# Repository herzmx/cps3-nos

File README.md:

# CPS3 NOS (NOR Open SIMM)

CPS3 NOS is an alternative to the original SIMMs for CPS3; currently, the available options include clone SIMMs with old-stock FLASH memory and Ultra SIMMs by DS. 

The project shares similarities with UltraSIMM but is not based on it. Instead, it is a new implementation built using publicly available pinouts and CPS3 schematics from FPGA projects.

The initial design aimed to use SPANSION NOR FLASH as the main memory, but this proved unfeasible due to speed limitations causing significant instability. As a result, MICRON NOR FLASH was used instead. While this is the same type of memory used in UltraSIMM and shares its pinout, but it's not directly compatible with UltraSIMM/UltraBIOS setup, because it is an entirely separate implementation.

The primary purpose of this project is to provide an alternative to SIMMs for catridges with original keys and battery, addressing the risks involved when updating the BIOS using the [CPS3 SIMM/CARTRIDGE PORT ADAPTER for OSCR](https://github.com/herzmx/CPS3-OSCR-Adapter). This project is not intended to create a new multi-SIMM solution. Given this primary purpose, it is very likely that UltraSIMM would also works on catridges with original keys and battery, though I do not have access to one to confirm.

## Issue Detected on 128MB NOS Module (Resolved)

An issue was previously identified with the 128MB NOS module, causing intermittent problems after extended use and potentially impacting game performance.

This has been fixed by replacing the LS148 logic with LVC00 and LVC08 gates to handle bank switching on the 128MB memory. This change improved response speed, resulting in consistent and stable reads.

If you built a module before this fix, we recommend updating to the latest source files.

## Assembly/Production  

Gerber, BOM, and POS files are provided in the `hw` directory. You can send them directly to a PCB fabrication company or assemble the boards yourself.  

When assembling, consider that the minimum pitch is **0.5mm**, and the footprint for capacitors and resistors is **0603**.

**Important!!!**, PCB tickness it's **1.2mm**

### 64MB SIMM  

For 64MB SIMMs, you can use the following parallel NOR FLASH memory chips:  

- **Micron MT28EW256/512/01G**  
- **Spansion S29256/512/GL01G** (use the 100ns speed version)  

### 128MB SIMM  

For 128MB SIMMs, only **Micron MT28EW01G** parallel NOR FLASH is supported. During development and testing, **Spansion** memory did not work as expected with bank switching on the 128MB SIMM.  

### Notes  

- Use only one type of SIMM when assembling a single **64MB SIMM**.  
- You can mix **Micron** and **Spansion** SIMMs if needed.  

## How to use

CPS3 can only handle four types of FLASH memory due to the instructions used for flashing new games through the system, these instructions are supported and coded in the BIOS.  

To make a new NOR FLASH memory compatible with CPS3, a BIOS patch is required.

### BIOS Patch

The **bios_patch.py** script allows you to apply patches to your current BIOS, adding compatibility for **SPANSION** and **MICRON** NOR FLASH.

For example, if you have a dump of *Street Fighter III 3rd Strike*, you can execute the following command to patch BIOS:

```bash
python bios_patch.py sfiii3_usa.29f400.u2 sfiii3
```

#### Compatibility Table

| Before patch | After patch          |
|--------------|----------------------|
| MXCI         | MXCI                 |
| SHARP/INTEL  | SHARP/INTEL          |
| HITACHI      | SPANSION             |
| MXIC         | MICRON NOS/UltraSIMM |

### Flashing Your New BIOS

Once the patch is applied, it's time to flash your updated BIOS onto the cartridge. There are two main methods you can use:

1. **Using the [CPS3 SIMM/CARTRIDGE PORT ADAPTER for OSCR](https://github.com/herzmx/CPS3-OSCR-Adapter)**  
   - This method works for both alive and death cartridges.
   - **NOTE**: Use it at your own risk on alive cartridges!

2. **Traditional Method**  
   - Remove the 29F400 chip from the cartridge and flash it using a programmer.  
   - This method is only recommended for death cartridges.

Now your cartdrige it's compatible with NOS!

### R/W CPS3 NOS 

Currently, CPS3 NOS can only be programmed using the [CPS3 SIMM/CARTRIDGE PORT ADAPTER for OSCR](https://github.com/herzmx/CPS3-OSCR-Adapter).

#### Prepare your files 

- **Dump or copy**  your CD-ROM files and organize them into a directory. For example, for *Street Fighter III: 2nd Impact*, the directory structure should look like this:

	```
    CDROM
    └── SFIII2
        ├── 10
        ├── 20
        ├── 30
        ├── 31
        ├── 40
        ├── 41
        ├── 50
        ├── 51
        ├── 90
        ├── 91
        ├── 92
        └── 93
	```

- Concatenate files for each SIMM
	- For **128M SIMMs**, use files 3# to 6#. 
	- For **64M SIMMs**, use files 10 and 20.
	
	 Example (using a Unix terminal):
	 
	 ```bash
	 	cat WAZARD/10WZ SFIII/10NG SFIII2/10 JOJO/10JO SFIII3B/103S2 JOJOBA/10JB > NOS10

		cat WAZARD/10WZFix SFIII/10NG SFIII2/10 JOJO/10JO SFIII3B/103S2 JOJOBA/10JB > NOS10
		
		cat WAZARD/20WZ SFIII/20NG SFIII2/20 JOJO/20JO SFIII3B/203S2 JOJOBA/20JB > NOS20
		
		cat WAZARD/30WZ WAZARD/31WZ SFIII/30NG SFIII/31NG SFIII2/30 SFIII2/31 JOJO/30JO JOJO/31JO SFIII3B/303S2 SFIII3B/313S2 JOJOBA/30JB JOJOBA/31JB > NOS30
		
		cat WAZARD/40WZ WAZARD/41WZ SFIII/40NG SFIII/41NG SFIII2/40 SFIII2/41 JOJO/40JO JOJO/41JO SFIII3B/403S2 SFIII3B/413S2 JOJOBA/40JB JOJOBA/41JB > NOS40
		
		cat WAZARD/50WZ WAZARD/51WZ SFIII/50NG SFIII/51NG SFIII2/50 SFIII2/51 JOJO/50JO JOJO/51JO SFIII3B/503S2 SFIII3B/513S2 JOJOBA/50JB JOJOBA/51JB > NOS50
		
		cat WAZARD/60WZ WAZARD/61WZ SFIII/60NG SFIII/61NG SFIII2/60 SFIII2/61 JOJO/60JO JOJO/61JO SFIII3B/603S2 SFIII3B/613S2 JOJOBA/60JB JOJOBA/61JB > NOS60
	 ```
	 
**Important Notes**
 
- NOS supports up to 8 titles. When using this feature, you must fill all SIMM slots and space.
- For example, when working with *Street Fighter III: New Generation*, you can duplicate certain files to fill all space:
- Use `10` as `20` for SIMM 2.
- Use `50` four times for SIMM 5.
- Use `40` as `60 `for SIMM 6.
 	
|                                             | 1      | 2      | 3       | 4       | 5       | 6       |
|---------------------------------------------|--------|--------|---------|---------|---------|---------|
| Street Fighter III: New Generation          | 64MBit | -      | 128MBit | 128MBit | 32MBit  | -       |
| Street Fighter III: New Generation (filled) | 64MBit | 64MBit | 128MBit | 128MBit | 128MBit | 128MBit |

Alternatively, you can use the **ds2nos.py** script to convert UltraSIMM files to NOS format.

#### Write NOS

The [CPS3 SIMM/CARTRIDGE PORT ADAPTER for OSCR](https://github.com/herzmx/CPS3-OSCR-Adapter) has designated slots for 64M and 128M SIMMs. Insert your NOS into the corresponding slot and connect the headers for additional addressing.

- Prepare your SD, copy NOS10* to NOS60* in root
- Use *Capcom System III* menu options to write files
- 128 MB

- 64 MB

### Install NOS on CPS3

- After writing all the NOS, install the SIMMs into the CPS3. It is recommended to label each SIMM to prevent any mix-ups in the future.

- Install the SW header to link all NOS if you plan to use more than one title.

### NOS SW Reference Table

| SW Config                   |        |
|-----------------------------|--------|
|  | GAME 1 |
|  | GAME 2 |
|  | GAME 3 |
|  | GAME 4 |
|  | GAME 5 |
|  | GAME 6 |
|  | GAME 7 |
|  | GAME 8 |

## Disclaimer!!!

**I am not responsible for any damage to your CPS3 cartridges or system. At this time, it remains untested in live cartridges, so use it at your own risk!**

## License
<br />This work is licensed under a <a rel="license" href="http://creativecommons.org/licenses/by-nc-sa/4.0/">Creative Commons Attribution-NonCommercial-ShareAlike 4.0 International</a>. You are able to reusers to distribute, remix, adapt, and build upon the material in any medium or format for noncommercial purposes only, and only so long as attribution is given. If you remix, adapt, or build upon the material, you must license the modified material under identical terms.

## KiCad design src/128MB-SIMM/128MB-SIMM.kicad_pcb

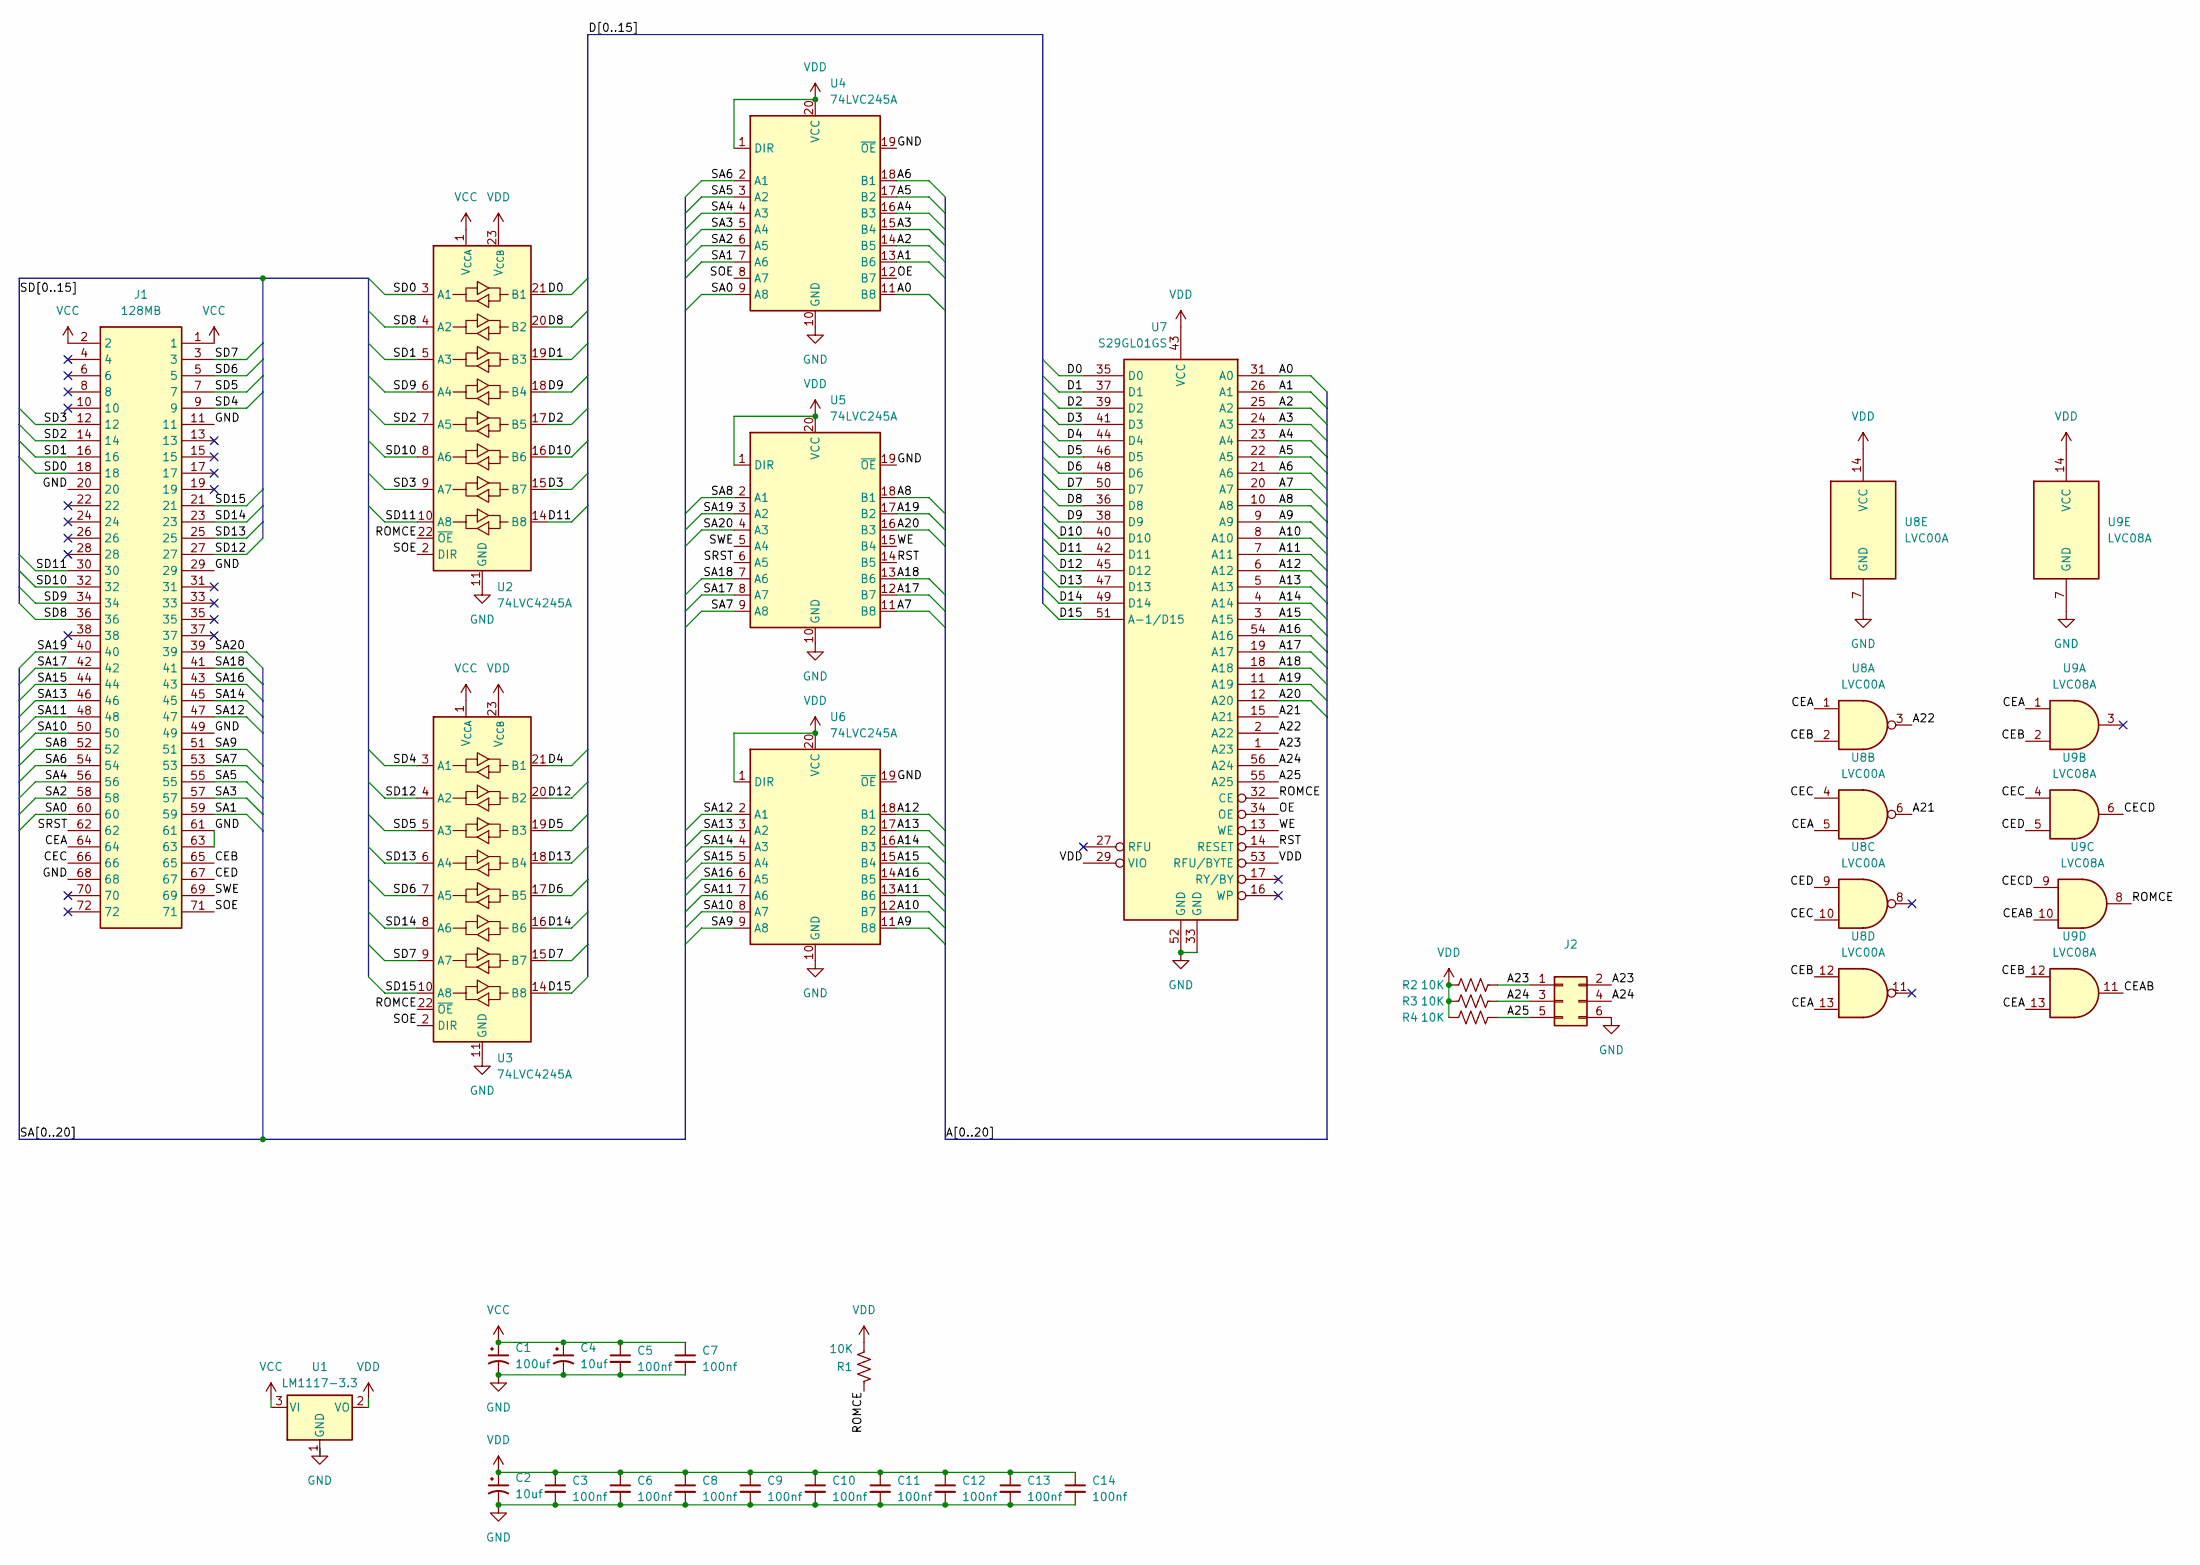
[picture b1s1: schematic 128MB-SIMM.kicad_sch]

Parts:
C1: 100uf; CP_EIA-3528-12_Kemet-T; LCSC C122271
C2, C4: 10uf; CP_EIA-3216-10_Kemet-I; LCSC C110052
C3, C5, C6, C7, C8, C9, C10, C11, C12, C13, C14: 100nf; C_0603_1608Metric; LCSC C14663
J1: 128MB; SIMM_EDGE; Manufacturer_Part_Number 5822030-3; Mouser Part Number 571-5822030-3
J2: Conn_02x03_Odd_Even; PinSocket_2x03_P1.27mm_Horizontal; LCSC C2881889
R1, R2, R3, R4: 10K; R_0603_1608Metric; LCSC C98220
U1: LM1117-3.3; SOT-223-3_TabPin2; LCSC C23984
U2, U3: 74LVC4245A; TSSOP-24_4.4x7.8mm_P0.65mm; LCSC C7859
U4, U5, U6: 74LVC245A; TSSOP-20_4.4x6.5mm_P0.65mm; LCSC C7848
U7: S29GL01GS; TSOP-I-56_18.4x14mm_P0.5mm; LCSC C2064354
U8: LVC00A; TSSOP-14_4.4x5mm_P0.65mm; LCSC C7803
U9: LVC08A; TSSOP-14_4.4x5mm_P0.65mm; LCSC C2867479

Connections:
/A0: U4.11 (B8), U7.31 (A0)
/A1: U4.13 (B6), U7.26 (A1)
/A2: U4.14 (B5), U7.25 (A2)
/A3: U4.15 (B4), U7.24 (A3)
/A4: U4.16 (B3), U7.23 (A4)
/A5: U4.17 (B2), U7.22 (A5)
/A6: U4.18 (B1), U7.21 (A6)
/A7: U5.11 (B8), U7.20 (A7)
/A8: U5.18 (B1), U7.10 (A8)
/A9: U6.11 (B8), U7.9 (A9)
/A10: U6.12 (B7), U7.8 (A10)
/A11: U6.13 (B6), U7.7 (A11)
/A12: U6.18 (B1), U7.6 (A12)
/A13: U6.17 (B2), U7.5 (A13)
/A14: U6.16 (B3), U7.4 (A14)
/A15: U6.15 (B4), U7.3 (A15)
/A16: U6.14 (B5), U7.54 (A16)
/A17: U5.12 (B7), U7.19 (A17)
/A18: U5.13 (B6), U7.18 (A18)
/A19: U5.17 (B2), U7.11 (A19)
/A20: U5.16 (B3), U7.12 (A20)
/A21: U7.15 (A21), U8.6
/A22: U7.2 (A22), U8.3
/A23: J2.1, J2.2, R2.2, U7.1 (A23)
/A24: J2.3, J2.4, R3.2, U7.56 (A24)
/A25: J2.5, R4.2, U7.55 (A25)
/CEA: J1.64, U8.1, U8.5, U8.13, U9.1, U9.13
/CEAB: U9.10, U9.11
/CEB: J1.65, U8.2, U8.12, U9.2, U9.12
/CEC: J1.66, U8.4, U8.10, U9.4
/CECD: U9.6, U9.9
/CED: J1.67, U8.9, U9.5
/D0: U2.21 (B1), U7.35 (D0)
/D1: U2.19 (B3), U7.37 (D1)
/D2: U2.17 (B5), U7.39 (D2)
/D3: U2.15 (B7), U7.41 (D3)
/D4: U3.21 (B1), U7.44 (D4)
/D5: U3.19 (B3), U7.46 (D5)
/D6: U3.17 (B5), U7.48 (D6)
/D7: U3.15 (B7), U7.50 (D7)
/D8: U2.20 (B2), U7.36 (D8)
/D9: U2.18 (B4), U7.38 (D9)
/D10: U2.16 (B6), U7.40 (D10)
/D11: U2.14 (B8), U7.42 (D11)
/D12: U3.20 (B2), U7.45 (D12)
/D13: U3.18 (B4), U7.47 (D13)
/D14: U3.16 (B6), U7.49 (D14)
/D15: U3.14 (B8), U7.51 (A-1/D15)
/OE: U4.12 (B7), U7.34 (OE)
/ROMCE: R1.1, U2.22 (~OE), U3.22 (~OE), U7.32 (CE), U9.8
/RST: U5.14 (B5), U7.14 (RESET)
/SA0: J1.60, U4.9 (A8)
/SA1: J1.59, U4.7 (A6)
/SA2: J1.58, U4.6 (A5)
/SA3: J1.57, U4.5 (A4)
/SA4: J1.56, U4.4 (A3)
/SA5: J1.55, U4.3 (A2)
/SA6: J1.54, U4.2 (A1)
/SA7: J1.53, U5.9 (A8)
/SA8: J1.52, U5.2 (A1)
/SA9: J1.51, U6.9 (A8)
/SA10: J1.50, U6.8 (A7)
/SA11: J1.48, U6.7 (A6)
/SA12: J1.47, U6.2 (A1)
/SA13: J1.46, U6.3 (A2)
/SA14: J1.45, U6.4 (A3)
/SA15: J1.44, U6.5 (A4)
/SA16: J1.43, U6.6 (A5)
/SA17: J1.42, U5.8 (A7)
/SA18: J1.41, U5.7 (A6)
/SA19: J1.40, U5.3 (A2)
/SA20: J1.39, U5.4 (A3)
/SD0: J1.18, U2.3 (A1)
/SD1: J1.16, U2.5 (A3)
/SD2: J1.14, U2.7 (A5)
/SD3: J1.12, U2.9 (A7)
/SD4: J1.9, U3.3 (A1)
/SD5: J1.7, U3.5 (A3)
/SD6: J1.5, U3.7 (A5)
/SD7: J1.3, U3.9 (A7)
/SD8: J1.36, U2.4 (A2)
/SD9: J1.34, U2.6 (A4)
/SD10: J1.32, U2.8 (A6)
/SD11: J1.30, U2.10 (A8)
/SD12: J1.27, U3.4 (A2)
/SD13: J1.25, U3.6 (A4)
/SD14: J1.23, U3.8 (A6)
/SD15: J1.21, U3.10 (A8)
/SOE: J1.71, U2.2 (DIR), U3.2 (DIR), U4.8 (A7)
/SRST: J1.62, U5.6 (A5)
/SWE: J1.69, U5.5 (A4)
/WE: U5.15 (B4), U7.13 (WE)
GND: C1.2, C2.2, C3.2, C4.2, C5.2, C6.2, C7.2, C8.2, C9.2, C10.2, C11.2, C12.2, C13.2, C14.2, J1.11, J1.20, J1.29, J1.49, J1.61, J1.63, J1.68, J2.6, U1.1 (GND), U2.11 (GND), U2.12 (GND), U2.13 (GND), U3.11 (GND), U3.12 (GND), U3.13 (GND), U4.10 (GND), U4.19 (~OE), U5.10 (GND), U5.19 (~OE), U6.10 (GND), U6.19 (~OE), U7.33 (GND), U7.52 (GND), U8.7 (GND), U9.7 (GND)
VCC: C1.1, C4.1, C5.1, C7.1, J1.1, J1.2, U1.3 (VI), U2.1 (V_{CCA}), U3.1 (V_{CCA})
VDD: C2.1, C3.1, C6.1, C8.1, C9.1, C10.1, C11.1, C12.1, C13.1, C14.1, R1.2, R2.1, R3.1, R4.1, U1.2 (VO), U2.23 (V_{CCB}), U2.24 (V_{CCB}), U3.23 (V_{CCB}), U3.24 (V_{CCB}), U4.1 (DIR), U4.20 (VCC), U5.1 (DIR), U5.20 (VCC), U6.1 (DIR), U6.20 (VCC), U7.29 (VIO), U7.43 (VCC), U7.53 (RFU/BYTE), U8.14 (VCC), U9.14 (VCC)

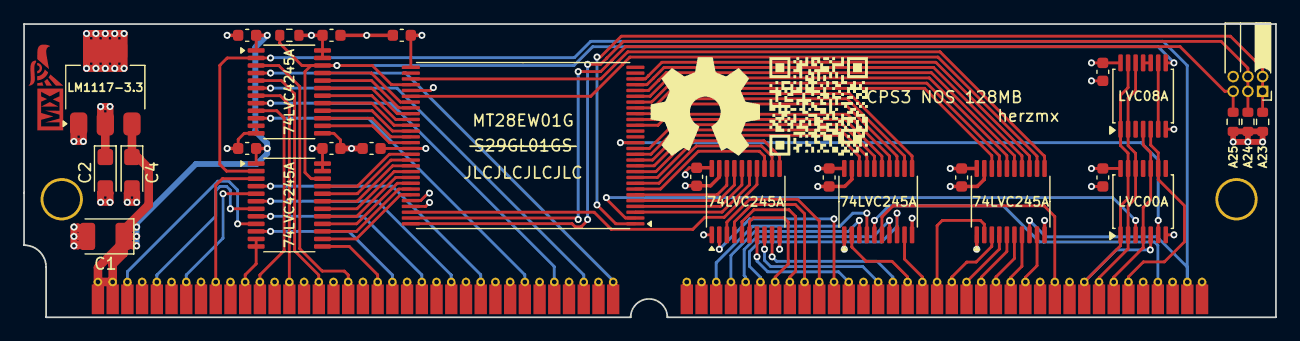
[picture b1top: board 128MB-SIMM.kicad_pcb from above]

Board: 4 copper layers, 108.0 x 25.3 mm, 29 parts (1 on the bottom side), 95 nets.

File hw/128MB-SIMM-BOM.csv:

Comment,Designator,Footprint,LCSC
100uf,C1,Capacitor_Tantalum_SMD:CP_EIA-3528-12_Kemet-T,C122271
10uf,"C2,C3",Capacitor_Tantalum_SMD:CP_EIA-3216-10_Kemet-I,C110052
100nf,"C4,C5,C6,C7,C8,C9,C10,C11,C12,C13,C14",Capacitor_SMD:C_0603_1608Metric,C14663
Conn_02x03_Odd_Even,J2,Connector_PinSocket_1.27mm:PinSocket_2x03_P1.27mm_Horizontal,C2881889
10K,"R1,R2,R3,R4,R5",Resistor_SMD:R_0603_1608Metric,C98220
LM1117-3.3,U1,Package_TO_SOT_SMD:SOT-223-3_TabPin2,C23984
74LVC4245A,"U2,U3",Package_SO:TSSOP-24_4.4x7.8mm_P0.65mm,C7859
S29GL01GS,U4,Package_SO:TSOP-I-56_18.4x14mm_P0.5mm,C2064354 
74LVC245A,"U5,U6,U7,U8",Package_SO:TSSOP-20_4.4x6.5mm_P0.65mm,C7848
74LS148,U9,Package_SO:SOIC-16_3.9x9.9mm_P1.27mm,C2674594

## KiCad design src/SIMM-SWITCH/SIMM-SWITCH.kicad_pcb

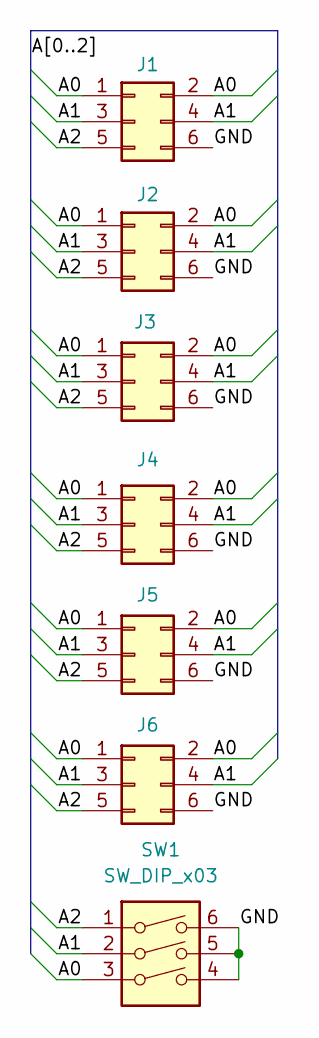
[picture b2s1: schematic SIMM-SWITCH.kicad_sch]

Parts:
J1, J2, J3, J4, J5, J6: Conn_02x03_Odd_Even; PinHeader_2x03_P1.27mm_Vertical_SMD; LCSC C2881908
SW1: SW_DIP_x03; SW-SMD_6P-L8.6-W6.2-P2.54-LS9.8; LCSC C319040

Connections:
/A0: J1.1, J1.2, J2.1, J2.2, J3.1, J3.2, J4.1, J4.2, J5.1, J5.2, J6.1, J6.2, SW1.3
/A1: J1.3, J1.4, J2.3, J2.4, J3.3, J3.4, J4.3, J4.4, J5.3, J5.4, J6.3, J6.4, SW1.2
/A2: J1.5, J2.5, J3.5, J4.5, J5.5, J6.5, SW1.1
/GND: J1.6, J2.6, J3.6, J4.6, J5.6, J6.6, SW1.4, SW1.5, SW1.6

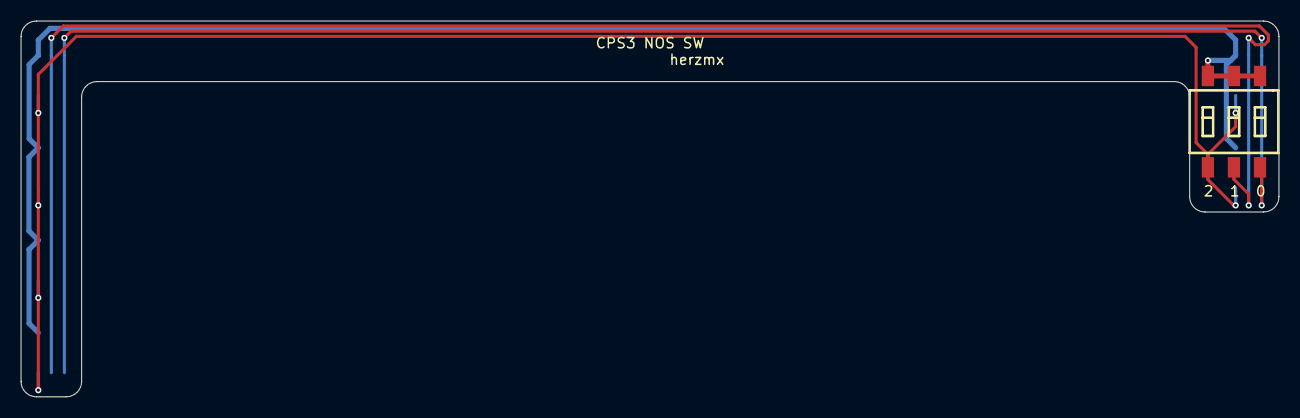
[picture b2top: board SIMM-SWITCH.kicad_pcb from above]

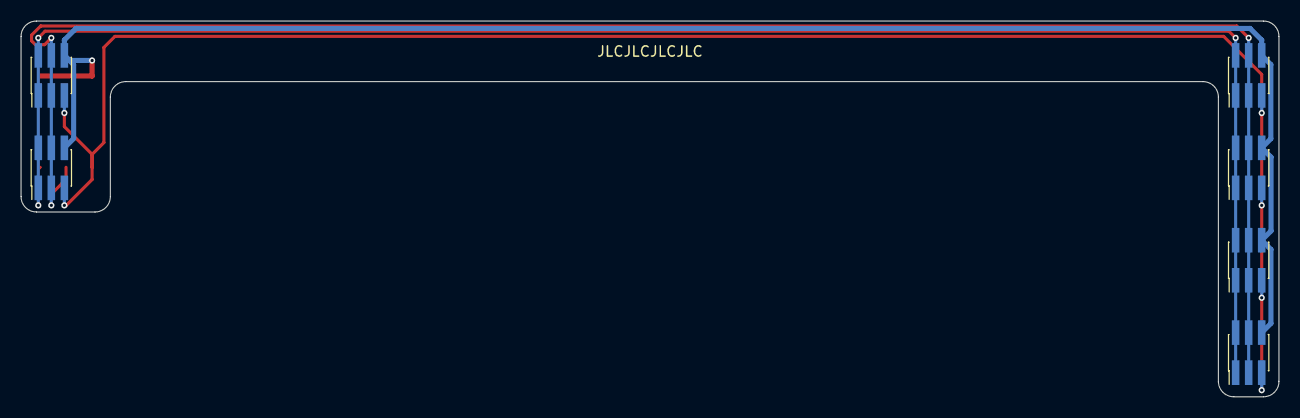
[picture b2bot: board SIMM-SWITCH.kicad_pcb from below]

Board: 2 copper layers, 122.5 x 36.6 mm, 7 parts (6 on the bottom side), 4 nets.

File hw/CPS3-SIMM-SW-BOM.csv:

Comment,Designator,Footprint,LCSC
Conn_02x03_Odd_Even,"J1,J2,J3,J4,J5,J6",Connector_PinHeader_1.27mm:PinHeader_2x03_P1.27mm_Vertical_SMD,C5160759
SW_DIP_x03,SW1,CPS3:SW-SMD_6P-L8.6-W6.2-P2.54-LS9.8,C319040

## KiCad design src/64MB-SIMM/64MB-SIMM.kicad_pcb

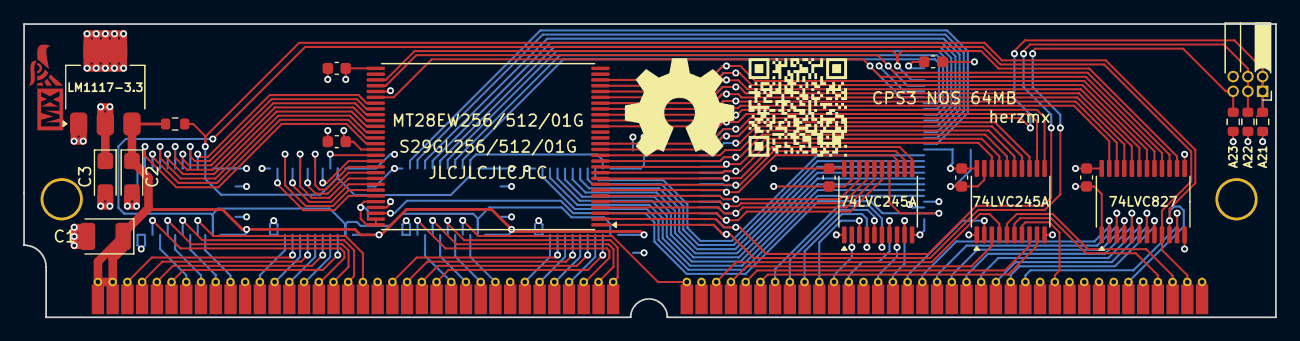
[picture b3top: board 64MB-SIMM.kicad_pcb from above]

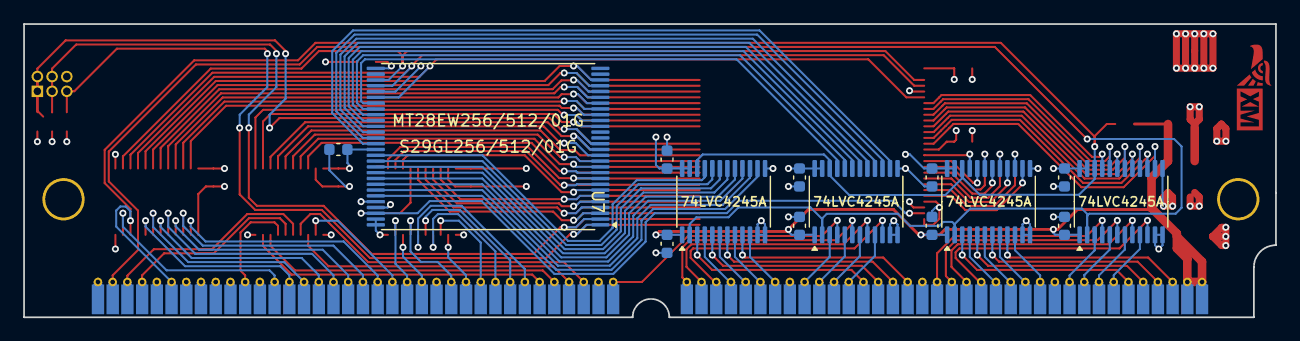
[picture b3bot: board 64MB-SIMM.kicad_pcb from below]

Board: 4 copper layers, 108.0 x 25.3 mm, 34 parts (15 on the bottom side), 122 nets.

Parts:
C1: 100uf; CP_EIA-3528-12_Kemet-T
C2, C3: 10uf; CP_EIA-3216-10_Kemet-I
C4, C5, C6, C7, C8, C9, C10, C11, C12, C13, C14, C15, C16, C17, C18: 100nf; C_0603_1608Metric
J1: 64MB; SIMM_EDGE
J2: Conn_02x03_Odd_Even; PinSocket_2x03_P1.27mm_Horizontal
R1, R2, R3, R4: 10K; R_0603_1608Metric
U1: LM1117-3.3; SOT-223-3_TabPin2
U2, U3, U7, U9: 74LVC4245A; TSSOP-24_4.4x7.8mm_P0.65mm
U4, U10: S29GL256/512/01G; TSOP-I-56_18.4x14mm_P0.5mm
U5, U6: 74LVC245A; TSSOP-20_4.4x6.5mm_P0.65mm
U8: 74LVC827; TSSOP-24_4.4x7.8mm_P0.65mm

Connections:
/A0: U4.31 (A0), U8.14 (Y10), U10.31 (A0)
/A1: U4.26 (A1), U8.17 (Y7), U10.26 (A1)
/A2: U4.25 (A2), U8.18 (Y6), U10.25 (A2)
/A3: U4.24 (A3), U8.19 (Y5), U10.24 (A3)
/A4: U4.23 (A4), U8.20 (Y4), U10.23 (A4)
/A5: U4.22 (A5), U8.21 (Y3), U10.22 (A5)
/A6: U4.21 (A6), U8.22 (Y2), U10.21 (A6)
/A7: U4.20 (A7), U8.23 (Y1), U10.20 (A7)
/A8: U4.10 (A8), U6.18 (B1), U10.10 (A8)
/A9: U4.9 (A9), U5.11 (B8), U10.9 (A9)
/A10: U4.8 (A10), U5.12 (B7), U10.8 (A10)
/A11: U4.7 (A11), U5.13 (B6), U10.7 (A11)
/A12: U4.6 (A12), U5.18 (B1), U10.6 (A12)
/A13: U4.5 (A13), U5.17 (B2), U10.5 (A13)
/A14: U4.4 (A14), U5.16 (B3), U10.4 (A14)
/A15: U4.3 (A15), U5.15 (B4), U10.3 (A15)
/A16: U4.54 (A16), U5.14 (B5), U10.54 (A16)
/A17: U4.19 (A17), U6.11 (B8), U10.19 (A17)
/A18: U4.18 (A18), U6.12 (B7), U10.18 (A18)
/A19: U4.11 (A19), U6.17 (B2), U10.11 (A19)
/A20: U4.12 (A20), U6.16 (B3), U10.12 (A20)
/A21: J2.1, J2.2, R1.2, U4.15 (A21), U10.15 (A21)
/A22: J2.3, J2.4, R2.2, U4.2 (A22), U10.2 (A22)
/A23: J2.5, R3.2, U4.1 (A23), U10.1 (A23)
/CE: U4.32 (CE), U8.15 (Y9), U10.32 (CE)
/OE: U4.34 (OE), U8.16 (Y8), U10.34 (OE)
/RST: U4.14 (RESET), U6.13 (B6), U10.14 (RESET)
/SA0: J1.60, U8.11 (A10)
/SA1: J1.59, U8.8 (A7)
/SA2: J1.58, U8.7 (A6)
/SA3: J1.57, U8.6 (A5)
/SA4: J1.56, U8.5 (A4)
/SA5: J1.55, U8.4 (A3)
/SA6: J1.54, U8.3 (A2)
/SA7: J1.53, U8.2 (A1)
/SA8: J1.52, U6.2 (A1)
/SA9: J1.51, U5.9 (A8)
/SA10: J1.50, U5.8 (A7)
/SA11: J1.48, U5.7 (A6)
/SA12: J1.47, U5.2 (A1)
/SA13: J1.46, U5.3 (A2)
/SA14: J1.45, U5.4 (A3)
/SA15: J1.44, U5.5 (A4)
/SA16: J1.43, U5.6 (A5)
/SA17: J1.42, U6.9 (A8)
/SA18: J1.41, U6.8 (A7)
/SA19: J1.40, U6.3 (A2)
/SA20: J1.39, U6.4 (A3)
/SCE: J1.67, R4.2, U2.22 (~OE), U3.22 (~OE), U7.22 (~OE), U8.10 (A9), U9.22 (~OE)
/SHD0: U9.21 (B1), U10.35 (D0)
/SHD1: U9.19 (B3), U10.37 (D1)
/SHD2: U9.17 (B5), U10.39 (D2)
/SHD3: U9.15 (B7), U10.41 (D3)
/SHD4: U7.21 (B1), U10.44 (D4)
/SHD5: U7.19 (B3), U10.46 (D5)
/SHD6: U7.17 (B5), U10.48 (D6)
/SHD7: U7.15 (B7), U10.50 (D7)
/SHD8: U9.20 (B2), U10.36 (D8)
/SHD9: U9.18 (B4), U10.38 (D9)
/SHD10: U9.16 (B6), U10.40 (D10)
/SHD11: U9.14 (B8), U10.42 (D11)
/SHD12: U7.20 (B2), U10.45 (D12)
/SHD13: U7.18 (B4), U10.47 (D13)
/SHD14: U7.16 (B6), U10.49 (D14)
/SHD15: U7.14 (B8), U10.51 (A-1/D15)
/SND_AD0: U3.21 (B1), U4.35 (D0)
/SND_AD1: U3.19 (B3), U4.37 (D1)
/SND_AD2: U3.17 (B5), U4.39 (D2)
/SND_AD3: U3.15 (B7), U4.41 (D3)
/SND_AD4: U2.21 (B1), U4.44 (D4)
/SND_AD5: U2.19 (B3), U4.46 (D5)
/SND_AD6: U2.17 (B5), U4.48 (D6)
/SND_AD7: U2.15 (B7), U4.50 (D7)
/SND_AD8: U3.20 (B2), U4.36 (D8)
/SND_AD9: U3.18 (B4), U4.38 (D9)
/SND_AD10: U3.16 (B6), U4.40 (D10)
/SND_AD11: U3.14 (B8), U4.42 (D11)
/SND_AD12: U2.20 (B2), U4.45 (D12)
/SND_AD13: U2.18 (B4), U4.47 (D13)
/SND_AD14: U2.16 (B6), U4.49 (D14)
/SND_AD15: U2.14 (B8), U4.51 (A-1/D15)
/SOE: J1.71, U2.2 (DIR), U3.2 (DIR), U7.2 (DIR), U8.9 (A8), U9.2 (DIR)
/SRST: J1.62, U6.7 (A6)
/SSHD0: J1.28, U9.3 (A1)
/SSHD1: J1.27, U9.5 (A3)
/SSHD2: J1.26, U9.7 (A5)
/SSHD3: J1.25, U9.9 (A7)
/SSHD4: J1.24, U7.3 (A1)
/SSHD5: J1.23, U7.5 (A3)
/SSHD6: J1.22, U7.7 (A5)
/SSHD7: J1.21, U7.9 (A7)
/SSHD8: J1.37, U9.4 (A2)
/SSHD9: J1.36, U9.6 (A4)
/SSHD10: J1.35, U9.8 (A6)
/SSHD11: J1.34, U9.10 (A8)
/SSHD12: J1.33, U7.4 (A2)
/SSHD13: J1.32, U7.6 (A4)
/SSHD14: J1.31, U7.8 (A6)
/SSHD15: J1.30, U7.10 (A8)
/SSND_AD0: J1.10, U3.3 (A1)
/SSND_AD1: J1.9, U3.5 (A3)
/SSND_AD2: J1.8, U3.7 (A5)
/SSND_AD3: J1.7, U3.9 (A7)
/SSND_AD4: J1.6, U2.3 (A1)
/SSND_AD5: J1.5, U2.5 (A3)
/SSND_AD6: J1.4, U2.7 (A5)
/SSND_AD7: J1.3, U2.9 (A7)
/SSND_AD8: J1.19, U3.4 (A2)
/SSND_AD9: J1.18, U3.6 (A4)
/SSND_AD10: J1.17, U3.8 (A6)
/SSND_AD11: J1.16, U3.10 (A8)
/SSND_AD12: J1.15, U2.4 (A2)
/SSND_AD13: J1.14, U2.6 (A4)
/SSND_AD14: J1.13, U2.8 (A6)
/SSND_AD15: J1.12, U2.10 (A8)
/SWE_SH: J1.69, U6.6 (A5)
/SWE_SND: J1.70, U6.5 (A4)
/WE_SH: U6.14 (B5), U10.13 (WE)
/WE_SND: U4.13 (WE), U6.15 (B4)
GND: C1.2, C2.2, C3.2, C4.2, C5.2, C6.2, C7.2, C8.2, C9.2, C10.2, C11.2, C12.2, C13.2, C14.2, C15.2, C16.2, C17.2, C18.2, J1.11, J1.20, J1.29, J1.49, J1.61, J1.63, J1.68, J2.6, U1.1 (GND), U2.11 (GND), U2.12 (GND), U2.13 (GND), U3.11 (GND), U3.12 (GND), U3.13 (GND), U4.33 (GND), U4.52 (GND), U4.55 (A25), U4.56 (A24), U5.10 (GND), U5.19 (~OE), U6.10 (GND), U6.19 (~OE), U7.11 (GND), U7.12 (GND), U7.13 (GND), U8.1 (~OE1), U8.12 (GND), U8.13 (~OE2), U9.11 (GND), U9.12 (GND), U9.13 (GND), U10.33 (GND), U10.52 (GND), U10.55 (A25), U10.56 (A24)
VCC: C1.1, C2.1, C4.1, C6.1, C13.1, C14.1, J1.1, J1.2, R4.1, U1.3 (VI), U2.1 (V_{CCA}), U3.1 (V_{CCA}), U7.1 (V_{CCA}), U9.1 (V_{CCA})
VDD: C3.1, C5.1, C7.1, C8.1, C9.1, C10.1, C11.1, C12.1, C15.1, C16.1, C17.1, C18.1, R1.1, R2.1, R3.1, U1.2 (VO), U2.23 (V_{CCB}), U2.24 (V_{CCB}), U3.23 (V_{CCB}), U3.24 (V_{CCB}), U4.29 (VIO), U4.43 (VCC), U4.53 (RFU/BYTE), U5.1 (DIR), U5.20 (VCC), U6.1 (DIR), U6.20 (VCC), U7.23 (V_{CCB}), U7.24 (V_{CCB}), U8.24 (VCC), U9.23 (V_{CCB}), U9.24 (V_{CCB}), U10.29 (VIO), U10.43 (VCC), U10.53 (RFU/BYTE)

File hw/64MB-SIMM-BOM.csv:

Comment,Designator,Footprint,LCSC
100uf,C1,Capacitor_Tantalum_SMD:CP_EIA-3528-12_Kemet-T,C122271
10uf,"C2,C3",Capacitor_Tantalum_SMD:CP_EIA-3216-10_Kemet-I,C110052
100nf,"C4,C5,C6,C7,C8,C9,C10,C11,C12,C13,C14,C15,C16,C17,C18",Capacitor_SMD:C_0603_1608Metric,C14663
Conn_02x03_Odd_Even,J2,Connector_PinSocket_1.27mm:PinSocket_2x03_P1.27mm_Horizontal,C2881889
10K,"R1,R2,R3,R4",Resistor_SMD:R_0603_1608Metric,C98220
LM1117-3.3,U1,Package_TO_SOT_SMD:SOT-223-3_TabPin2,C23984
74LVC4245A,"U2,U3,U7,U9",Package_SO:TSSOP-24_4.4x7.8mm_P0.65mm,C7859
S29GL256S,"U4,U10",Package_SO:TSOP-I-56_18.4x14mm_P0.5mm,C598853
74LVC245A,"U5,U6",Package_SO:TSSOP-20_4.4x6.5mm_P0.65mm,C7848
74LVC827,U8,Package_SO:TSSOP-24_4.4x7.8mm_P0.65mm,C2652112

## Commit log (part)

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2022-12-05 Create symbols for SIMM and memory
2022-12-05 Create 64MB project
2022-12-05 Create 128MB project
2024-12-06 Updated symbols and added footprints
2024-12-06 Updated 128 SIMM for release
2024-12-06 Updated 64 SIMM for release
2024-12-06 Added SIMM SW to bank switch
2024-12-06 move src files
2024-12-06 Updated footprints
2024-12-06 update sw for release
2024-12-09 add release files
2025-01-07 Add help scripts
2025-01-07 Add README
2025-01-07 Upadte assets
2025-01-07 Update assets
2025-01-07 Update README 1.2mm tickness PCB
2025-01-07 add missing hw files
2025-01-08 Correct and full license is added
2025-01-08 add issue video
2026-06-20 update source files changed LS41 by LVC00 and LVC08
2026-06-20 update release files
